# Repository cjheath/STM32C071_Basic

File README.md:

# STM32C071_Basic

A template project for STM32 projects using the STM32C071 32-pin QFP, with USB and SWD.

## Goals and Status

This project provides a self-contained quick-start for projects
which require an easy-to-use USB-based micro-controller with Single-Wire-Debug (SWD),
such as for small test PCBs to evaluate new integrated circuit chips
that need configuration via SPI, I2C or UART
before integrating those chips into larger designs.

The following aspects are (to be) provided:

* Configuration
  - STM32CubeMX pin-configuration file you should edit for your required I/O configuration
* Hardware
  - KiCad schematic and 2-layer PCB containing the STM32, USB and SWD connectors
  - 3.3V Buck switcher from VBUS up to 20V (in case you use USB-PD)
  - KiCad project-local library of symbols, footprints and 3D models
  - LCSC ordering codes on all parts, to facilitate ordering on JLCPCB
* Firmware (incomplete)
  - Chip initialisation and peripheral setup firmware (NOT using the CubeMX-generated HAL code)
  - Basic USB device initialisation as a USB CDC-ish (USB serial) to support remote-control protocols
  - A Makefile for the firmware
* Host software (not started)
  - A simple command-line program for you to extend to add configuration commands

This template is still incomplete. Use at own risk

## How to use this template

View the README file in the Hardare directory. You may explore alternative MCU pin configurations
using either Kicad or by opening Configuration/STM32C071_Basic.ioc using STM32CubeMX.

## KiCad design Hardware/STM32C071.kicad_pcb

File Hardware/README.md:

# STM32C071_Basic Hardware

## Adapting the design to suit your project

Pin functions on the MCU are configured for minimum layout complexity
for UART, I2C and SPI, but KiCad knows what alternate functions are
possible. If you need different pin functions, you should reconfigure
them.

You may obviously change the size of the PCB by redrawing the Edge Cuts
rectangle.

## Libraries

This Kicad project has a local [project](project.kicad_sym) library and
uses [jlcbasic](https://github.com/cjheath/jlcbasic) and
[jlcpreferred](https://github.com/cjheath/jlcpreferred) libraries from
Github.  These libraries are expected to be checked-out somewhere
together, and this directory should contain a symbolic link to their
parent directory.  If you can't use a symbolic link, make the
(libraries)[libraries] directory and check out those projects inside
that.

## Hardware choices

So far as possible, parts are chosen to be easy for a relative novice to
hand-solder.  Accordingly, the smallest parts are 0805 packages, and the
MCU is a QFP, not a leadless version.  The cheapest possible parts have
been chosen throughout, with a preference for JLCPCB parts that have no
extra assembly changes.

# Power supply

The 3.2V power supply should be capable of more than 700mA, which is all
the power that 5V USB guarantees.  If you intend to use this much power,
you should increase the size of the tantalum capacitor on the output.

The power supply is designed to sink heat to the grond plane on the back
of the board. You might wish to remove the ground plane elsewhere, but
consider leaving it in this area if you need low noise or heatsinking.

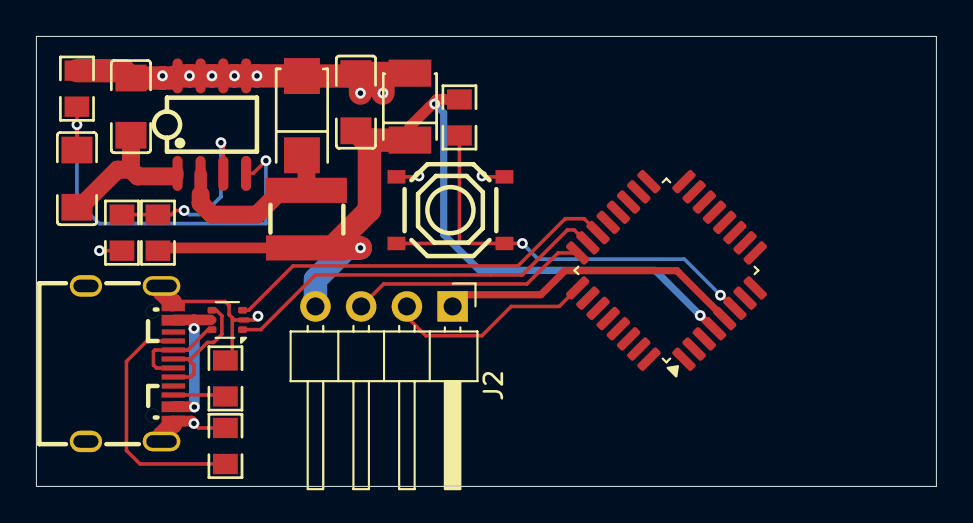
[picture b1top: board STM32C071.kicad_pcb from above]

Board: 2 copper layers, 50.0 x 25.0 mm, 18 parts (0 on the bottom side), 15 nets.

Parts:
C2: 100uF; CASE-B_3528
C3, C4, C5: 10uF; C1206
D1: SS34; SMA_L4.3-W2.6-LS5.2-RD
J1: USB_C_Receptacle_USB2.0_16P; USB-C-SMD_TYPE-C-USB-17
J2: Conn_01x04_Pin; PinHeader_1x04_P2.54mm_Horizontal
L1: 100uH; IND-SMD_L4.0-W4.0_SMNR4030
R1, R2: 5.1kΩ; R0805
R3: 2.7kΩ; R0805
R4: 4.7kΩ; R0805
R5, R6: 22kΩ; R0805
SW1: TS-1187A-B-A-B; SW-SMD_4P-L5.1-W5.1-P3.70-LS6.5-TL_H1.5
U1: STM32C071K8Tx; LQFP-32_7x7mm_P0.8mm
U2: USBLC6-2P6; SOT-666
U4: XL1509-ADJE1; SOIC-8_L5.0-W4.0-P1.27-LS6.0-BL

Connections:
+3.3V: C2.1, C5.2, J2.4, L1.2, R4.2, R6.1, U1.4 (VDD)
GND: C2.2, C3.1, C5.1, D1.2 (A), J1.0, J1.A1 (GND), J1.A12 (GND), J2.1, R1.1, R2.2, R3.1, R5.2, SW1.3 (C), SW1.4 (D), U1.5 (VSS), U2.2 (GND), U4.5 (GND), U4.6 (GND), U4.7 (GND), U4.8 (GND)
NRST: R6.2, SW1.1 (A), SW1.2 (B), U1.6 (NRST)
unnamed: D1.1 (K), L1.1, U4.2 (OUT)
unnamed: J1.A5 (CC1), R2.1
unnamed: J1.B5 (CC2), R1.2
unnamed: J1.A6 (D+), J1.B6 (D+), U2.6 (I/O1)
unnamed: J1.A7 (D-), J1.B7 (D-), U2.4 (I/O2)
unnamed: J2.2, U1.25 (DEBUG_SWCLK)
unnamed: J2.3, U1.24 (DEBUG_SWDIO)
unnamed: U1.22 (USB_DM), U2.3 (I/O2)
unnamed: U1.23 (USB_DP), U2.1 (I/O1)
unnamed: R3.2, R4.1, U4.3 (FB)
unnamed: C4.1, R5.1, U4.4 (ON/OFF)
VBUS: C3.2, C4.2, J1.A4 (VBUS), J1.A9 (VBUS), U2.5 (VBUS), U4.1 (VIN)

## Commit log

2025-04-24 Initial Pin selection
2025-05-03 Added Kicad schematic with STM32C071 symbol adapted to the chosen pinout configuration
2025-05-03 Added libraries, CPU and USB hookup
2025-05-04 Geometry
2025-05-05 Added README.md
2025-05-19 Added TPS5430 power supply. No decoupling or input caps yet
2025-05-19 Added library paths
2025-05-19 Add complete firmware files
2025-05-19 More work on power supply
2025-05-19 Cleaned up old STMCube-generated firmware
2025-05-19 Added 2n7002 to drive the power-on FET
2025-05-20 Changed power supply to XL1509. Started PCB. No inductor yet
2025-05-21 New Power supply and USB connector laid out
2025-05-21 Corrected STM32 file names
2025-05-21 Added SWD connector and 3D view
2025-05-21 Fixed project library paths
2025-05-22 Added README entries to aid new users
2025-05-22 Added Reset and power connections, 45 rotation
2025-05-26 Grounded USB-C mounting pins
